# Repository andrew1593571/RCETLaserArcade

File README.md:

# Laser-Arcade-Project
All documentation of the Laser Arcade Project

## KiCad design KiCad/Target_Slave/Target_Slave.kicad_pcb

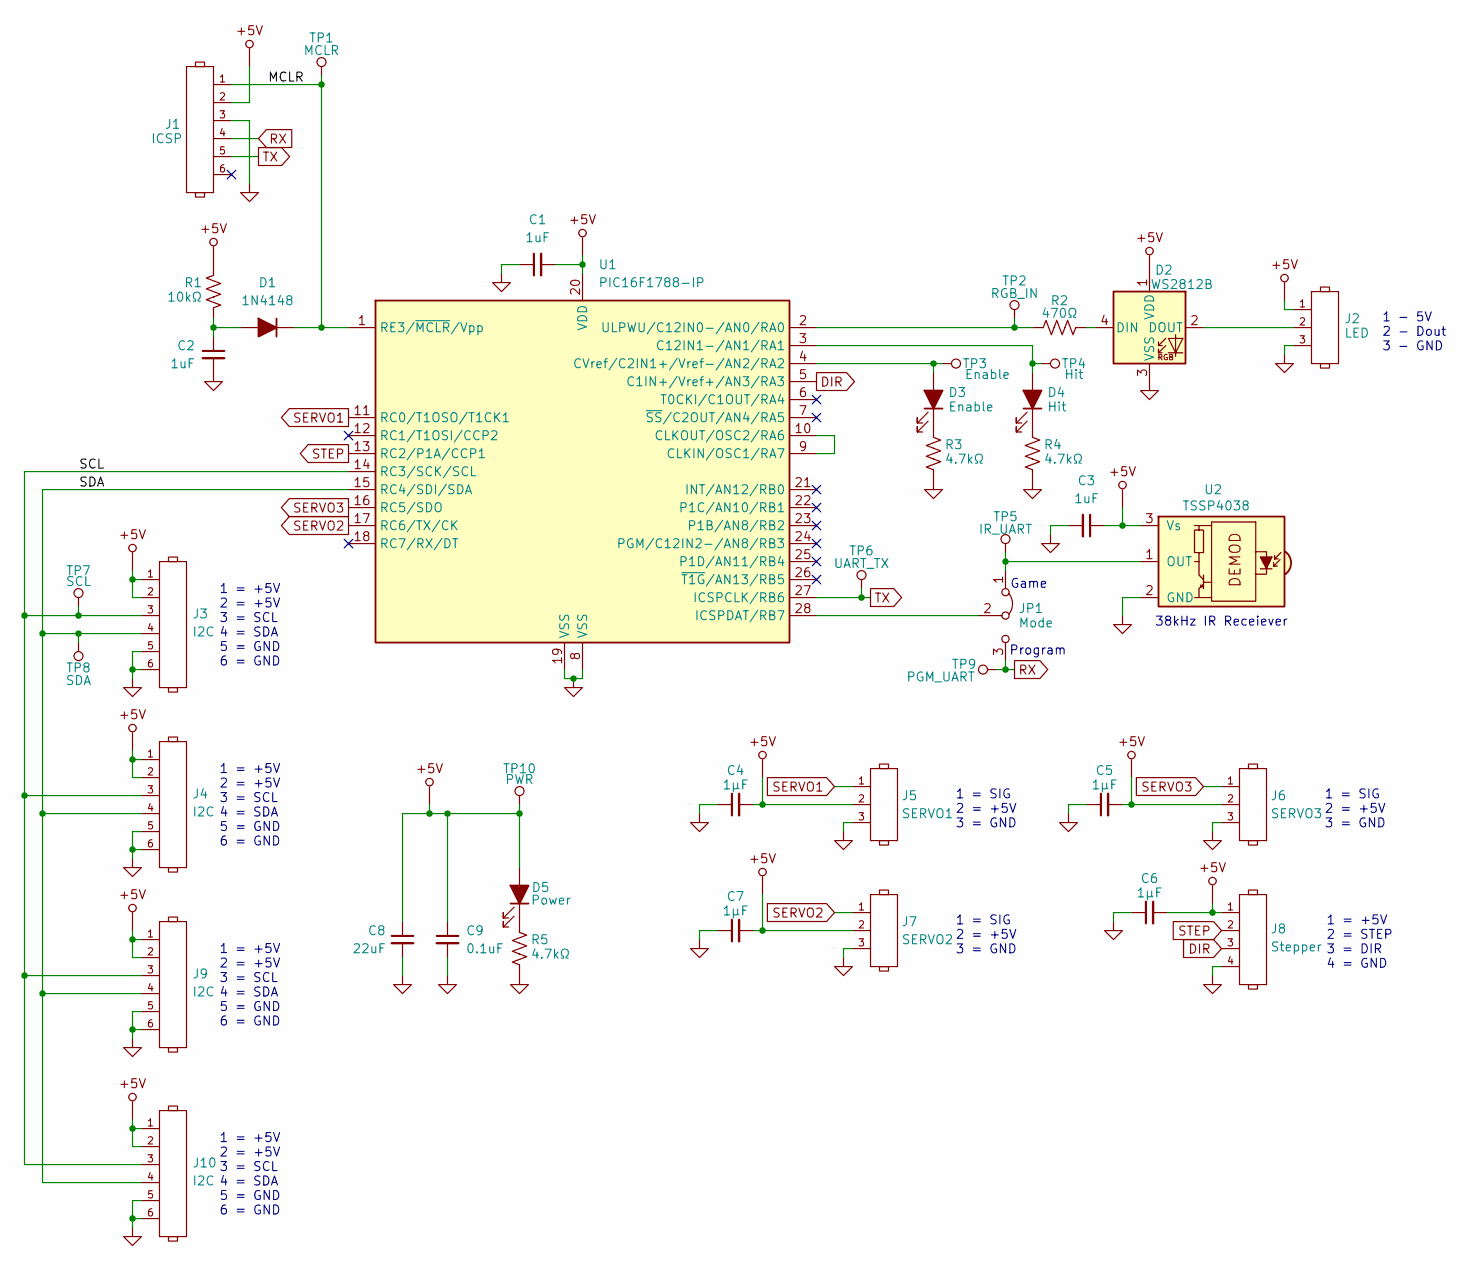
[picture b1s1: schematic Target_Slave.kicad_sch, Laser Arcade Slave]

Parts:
C1, C2, C3: 1uF; C_0805_2012Metric_Pad1.18x1.45mm_HandSolder
C4, C5, C6, C7: 1µF; C_0805_2012Metric_Pad1.18x1.45mm_HandSolder
C8: 22uF; C_0805_2012Metric_Pad1.18x1.45mm_HandSolder
C9: 0.1uF; C_0805_2012Metric_Pad1.18x1.45mm_HandSolder
D1: 1N4148; D_0805_2012Metric_Pad1.15x1.40mm_HandSolder
D2: WS2812B; LED_WS2812B_PLCC4_5.0x5.0mm_P3.2mm
D3: Enable; LED_0805_2012Metric_Pad1.15x1.40mm_HandSolder
D4: Hit; LED_0805_2012Metric_Pad1.15x1.40mm_HandSolder
D5: Power; LED_0805_2012Metric_Pad1.15x1.40mm_HandSolder
J1: ICSP; 1x6_100mil_Header
J2: LED; 1x3_100mil_Header_Locking
J3, J4, J9, J10: I2C; 1x6_100mil_Header
J5: SERVO1; 1x3_100mil_Header
J6: SERVO3; 1x3_100mil_Header
J7: SERVO2; 1x3_100mil_Header
J8: Stepper; 1x4_100mil_Header
JP1: Mode; 1x3_100mil_Header
R1: 10kΩ; R_0805_2012Metric_Pad1.20x1.40mm_HandSolder
R2: 470Ω; R_0805_2012Metric_Pad1.20x1.40mm_HandSolder
R3, R4, R5: 4.7kΩ; R_0805_2012Metric_Pad1.20x1.40mm_HandSolder
TP1: MCLR; 1x1_100mil_Header
TP2: RGB_IN; 1x1_100mil_Header
TP3: Enable; 1x1_100mil_Header
TP4: Hit; 1x1_100mil_Header
TP5: IR_UART; 1x1_100mil_Header
TP6: UART_TX; 1x1_100mil_Header
TP7: SCL; 1x1_100mil_Header
TP8: SDA; 1x1_100mil_Header
TP9: PGM_UART; 1x1_100mil_Header
TP10: PWR; 1x1_100mil_Header
U1: PIC16F1788-IP; SSOP-28
U2: TSSP4038; IR Receiver

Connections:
+5V: C1.2, C3.1, C4.2, C5.2, C6.2, C7.2, C8.1, C9.1, D2.1 (VDD), D5.2 (A), J1.2, J2.1, J3.1, J3.2, J4.1, J4.2, J5.2, J6.2, J7.2, J8.1, J9.1, J9.2, J10.1, J10.2, R1.1, TP10.1, U1.20 (VDD), U2.3 (Vs)
/MCLR: D1.1 (K), J1.1, TP1.1, U1.1 (RE3/~MCLR/Vpp)
/SCL: J3.3, J4.3, J9.3, J10.3, TP7.1, U1.14 (RC3/SCK/SCL)
/SDA: J3.4, J4.4, J9.4, J10.4, TP8.1, U1.15 (RC4/SDI/SDA)
DIR: J8.3, U1.5 (C1IN+/Vref+/AN3/RA3)
GND: C1.1, C2.2, C3.2, C4.1, C5.1, C6.1, C7.1, C8.2, C9.2, D2.3 (VSS), J1.3, J2.3, J3.5, J3.6, J4.5, J4.6, J5.3, J6.3, J7.3, J8.4, J9.5, J9.6, J10.5, J10.6, R3.2, R4.2, R5.2, U1.8 (VSS), U1.19 (VSS), U2.2 (GND)
unnamed: C2.1, D1.2 (A), R1.2
unnamed: D2.4 (DIN), R2.2
unnamed: D2.2 (DOUT), J2.2
unnamed: D3.2 (A), TP3.1, U1.4 (CVref/C2IN1+/Vref-/AN2/RA2)
unnamed: D3.1 (K), R3.1
unnamed: D4.2 (A), TP4.1, U1.3 (C12IN1-/AN1/RA1)
unnamed: D4.1 (K), R4.1
unnamed: D5.1 (K), R5.1
unnamed: JP1.1 (A), TP5.1, U2.1 (OUT)
unnamed: JP1.2 (C), U1.28 (ICSPDAT/RB7)
unnamed: U1.9 (CLKIN/OSC1/RA7), U1.10 (CLKOUT/OSC2/RA6)
unnamed: R2.1, TP2.1, U1.2 (ULPWU/C12IN0-/AN0/RA0)
RX: J1.4, JP1.3 (B), TP9.1
SERVO1: J5.1, U1.11 (RC0/T1OSO/T1CK1)
SERVO2: J7.1, U1.17 (RC6/TX/CK)
SERVO3: J6.1, U1.16 (RC5/SDO)
STEP: J8.2, U1.13 (RC2/P1A/CCP1)
TX: J1.5, TP6.1, U1.27 (ICSPCLK/RB6)

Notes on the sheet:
1 = +5V 2 = STEP 3 = DIR 4 = GND
1 = +5V 2 = +5V 3 = SCL 4 = SDA 5 = GND 6 = GND
Program
1 = SIG 2 = +5V 3 = GND
1 - 5V 2 - Dout 3 - GND
Game
38kHz IR Receiever

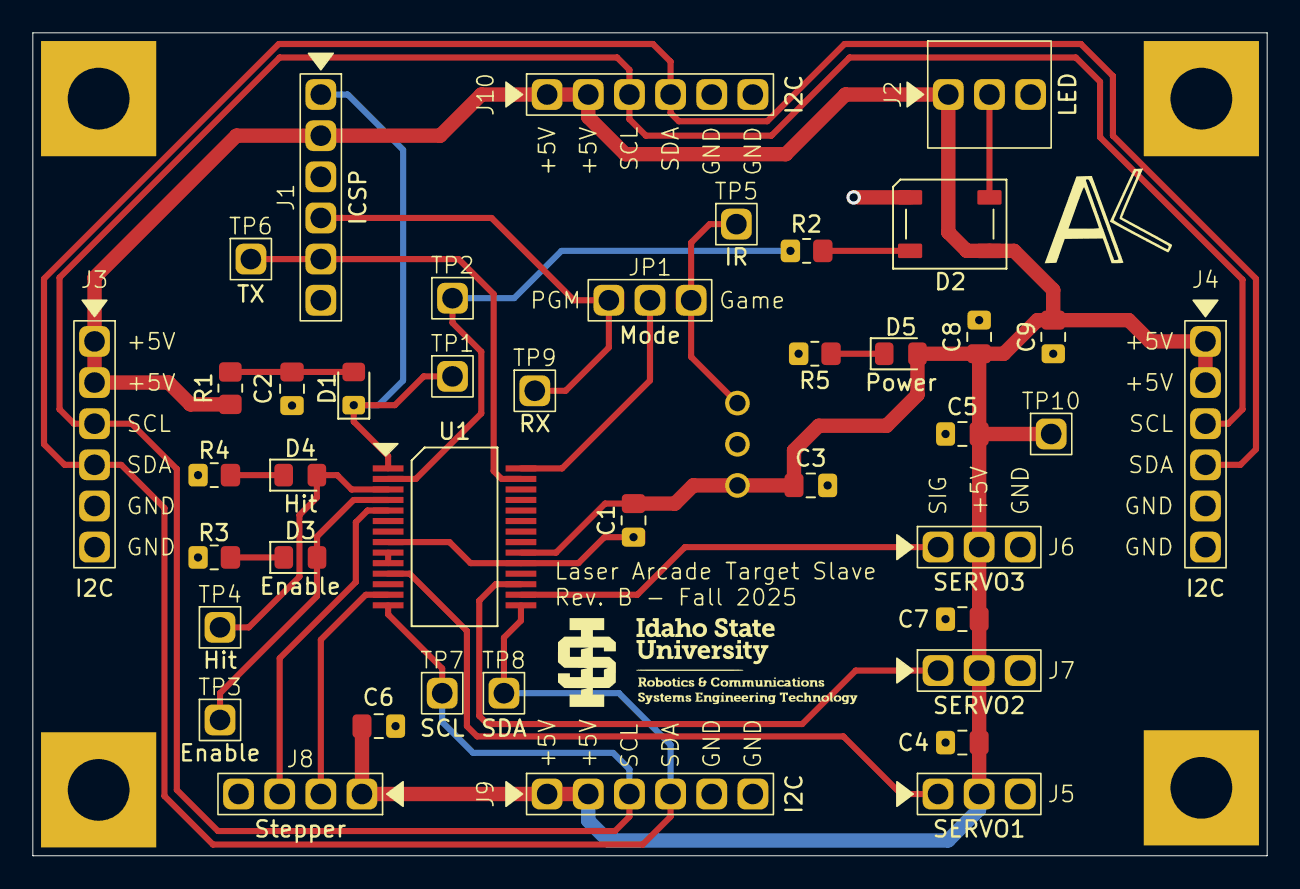
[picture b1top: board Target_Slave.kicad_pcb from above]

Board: 2 copper layers, 76.2 x 50.8 mm, 42 parts (1 on the bottom side), 24 nets.

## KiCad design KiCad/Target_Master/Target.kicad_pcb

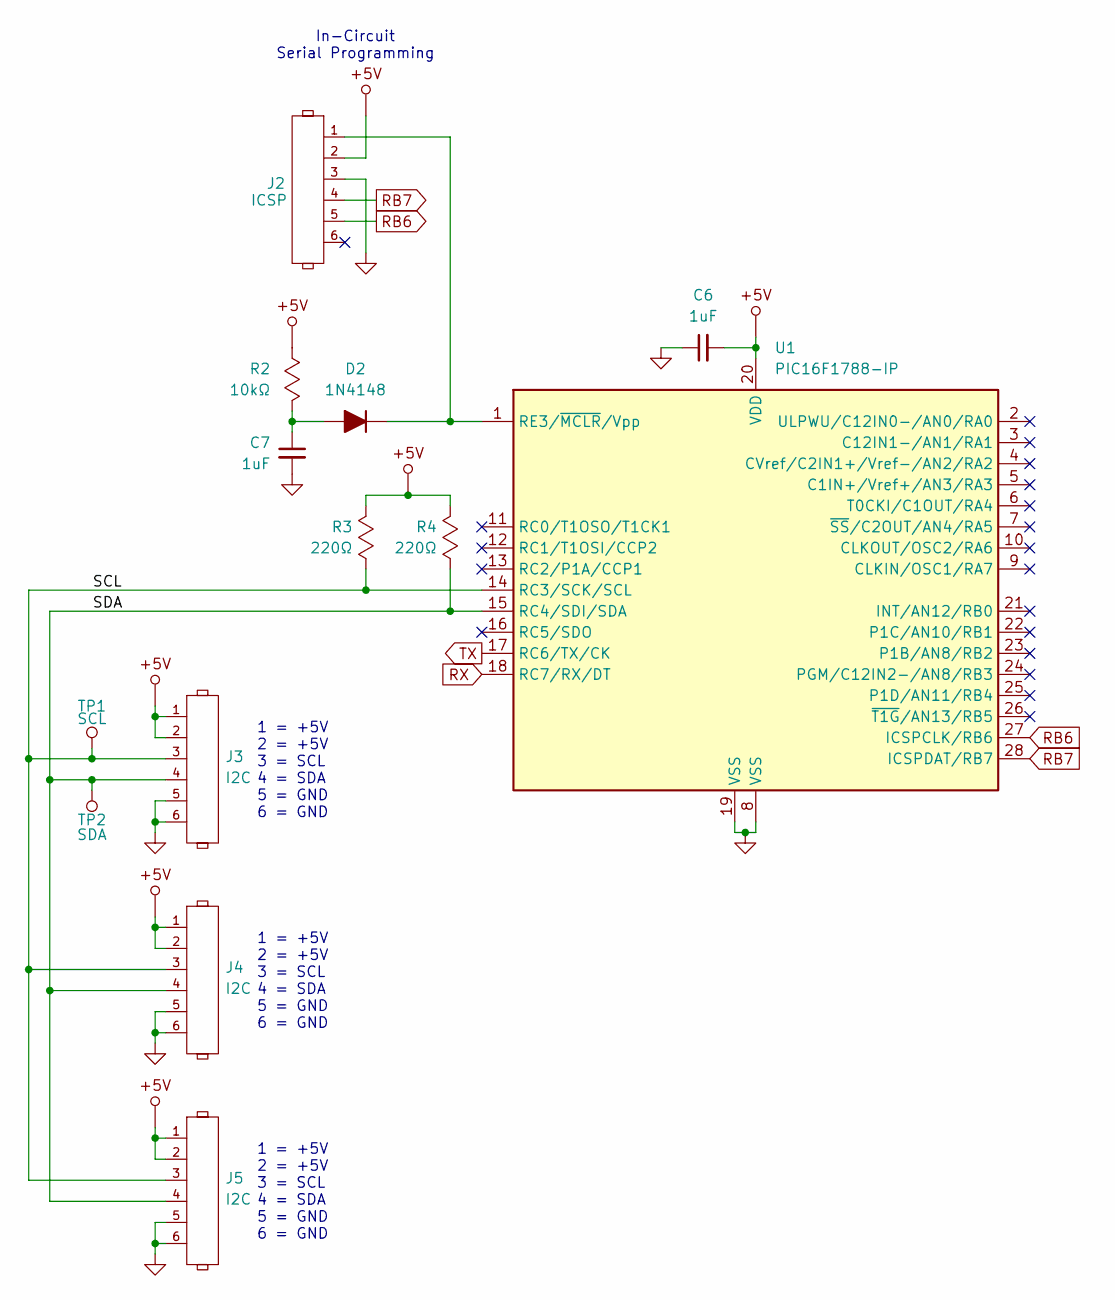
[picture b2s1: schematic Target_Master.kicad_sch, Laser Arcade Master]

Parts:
C6, C7: 1uF; C_0805_2012Metric_Pad1.18x1.45mm_HandSolder
D2: 1N4148; D_0805_2012Metric_Pad1.15x1.40mm_HandSolder
J2: ICSP; 1x6_100mil_Header
J3, J4, J5: I2C; 1x6_100mil_Header
R2: 10kΩ; R_0805_2012Metric_Pad1.20x1.40mm_HandSolder
R3, R4: 220Ω; R_0805_2012Metric_Pad1.20x1.40mm_HandSolder
TP1: SCL; 1x1_100mil_Header
TP2: SDA; 1x1_100mil_Header
U1: PIC16F1788-IP; SSOP-28

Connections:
+5V: C6.2, J2.2, J3.1, J3.2, J4.1, J4.2, J5.1, J5.2, R2.2, R3.1, R4.1, U1.20 (VDD); also elsewhere on the board
/Master/SCL: J3.3, J4.3, J5.3, R3.2, TP1.1, U1.14 (RC3/SCK/SCL)
/Master/SDA: J3.4, J4.4, J5.4, R4.2, TP2.1, U1.15 (RC4/SDI/SDA)
GND: C6.1, C7.2, J2.3, J3.5, J3.6, J4.5, J4.6, J5.5, J5.6, U1.8 (VSS), U1.19 (VSS); also elsewhere on the board
unnamed: C7.1, D2.2 (A), R2.1
unnamed: D2.1 (K), J2.1, U1.1 (RE3/~MCLR/Vpp)
RB6: J2.5, U1.27 (ICSPCLK/RB6)
RB7: J2.4, U1.28 (ICSPDAT/RB7)
RX: U1.18 (RC7/RX/DT); also elsewhere on the board
TX: U1.17 (RC6/TX/CK); also elsewhere on the board

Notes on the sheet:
In-Circuit Serial Programming
1 = +5V 2 = +5V 3 = SCL 4 = SDA 5 = GND 6 = GND

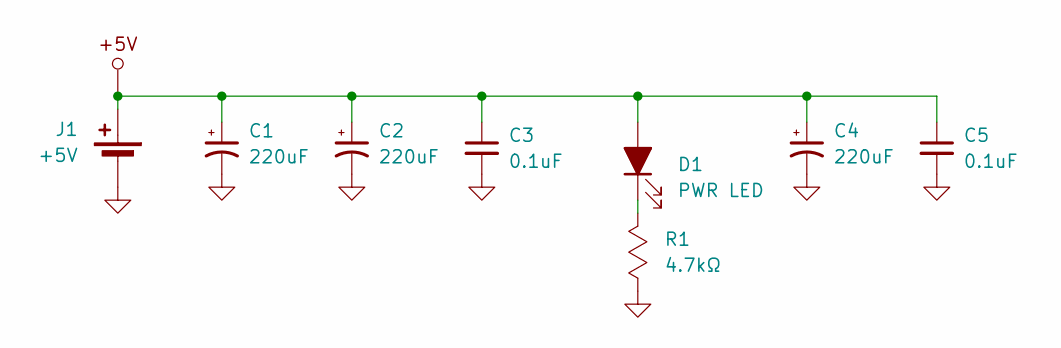
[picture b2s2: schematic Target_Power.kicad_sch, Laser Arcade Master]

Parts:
C1, C2, C4: 220uF; CP_Radial_D6.3mm_P2.50mm
C3, C5: 0.1uF; C_0805_2012Metric_Pad1.18x1.45mm_HandSolder
D1: PWR LED; LED_0805_2012Metric_Pad1.15x1.40mm_HandSolder
J1: +5V; AMASS_XT30PW-M_1x02_P2.50mm_Horizontal
R1: 4.7kΩ; R_0805_2012Metric_Pad1.20x1.40mm_HandSolder

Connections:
+5V: C1.1, C2.1, C3.1, C4.1, C5.1, D1.2 (A), J1.1 (+); also elsewhere on the board
GND: C1.2, C2.2, C3.2, C4.2, C5.2, J1.2 (-), R1.1; also elsewhere on the board
unnamed: D1.1 (K), R1.2

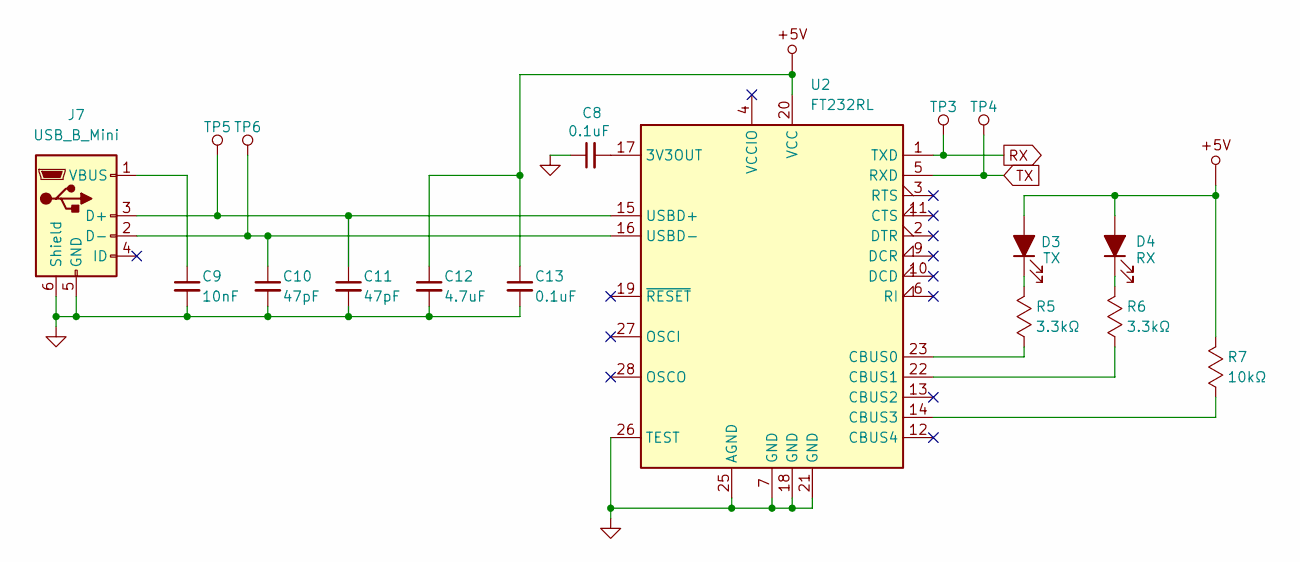
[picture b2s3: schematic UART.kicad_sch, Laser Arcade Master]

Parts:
C8, C13: 0.1uF; C_0805_2012Metric_Pad1.18x1.45mm_HandSolder
C9: 10nF; C_0805_2012Metric_Pad1.18x1.45mm_HandSolder
C10, C11: 47pF; C_0805_2012Metric_Pad1.18x1.45mm_HandSolder
C12: 4.7uF; C_0805_2012Metric_Pad1.18x1.45mm_HandSolder
D3: TX; LED_0805_2012Metric_Pad1.15x1.40mm_HandSolder
D4: RX; LED_0805_2012Metric_Pad1.15x1.40mm_HandSolder
J7: USB_B_Mini; USB_Micro-B_Amphenol
R5, R6: 3.3kΩ; R_0805_2012Metric_Pad1.20x1.40mm_HandSolder
R7: 10kΩ; R_0805_2012Metric_Pad1.20x1.40mm_HandSolder
TP3, TP4, TP5, TP6: 1x1_100mil_Header
U2: FT232RL; SSOP-28

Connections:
+5V: C12.1, C13.1, D3.2 (A), D4.2 (A), R7.2, U2.20 (VCC); also elsewhere on the board
GND: C8.1, C9.2, C10.2, C11.2, C12.2, C13.2, J7.5 (GND), J7.6 (Shield), U2.7 (GND), U2.18 (GND), U2.21 (GND), U2.25 (AGND), U2.26 (TEST); also elsewhere on the board
unnamed: D3.1 (K), R5.2
unnamed: D4.1 (K), R6.2
unnamed: C11.1, J7.3 (D+), TP5.1, U2.15 (USBD+)
unnamed: C10.1, J7.2 (D-), TP6.1, U2.16 (USBD-)
unnamed: C9.1, J7.1 (VBUS)
unnamed: C8.2, U2.17 (3V3OUT)
unnamed: R5.1, U2.23 (CBUS0)
unnamed: R6.1, U2.22 (CBUS1)
unnamed: R7.1, U2.14 (CBUS3)
RX: TP3.1, U2.1 (TXD); also elsewhere on the board
TX: TP4.1, U2.5 (RXD); also elsewhere on the board

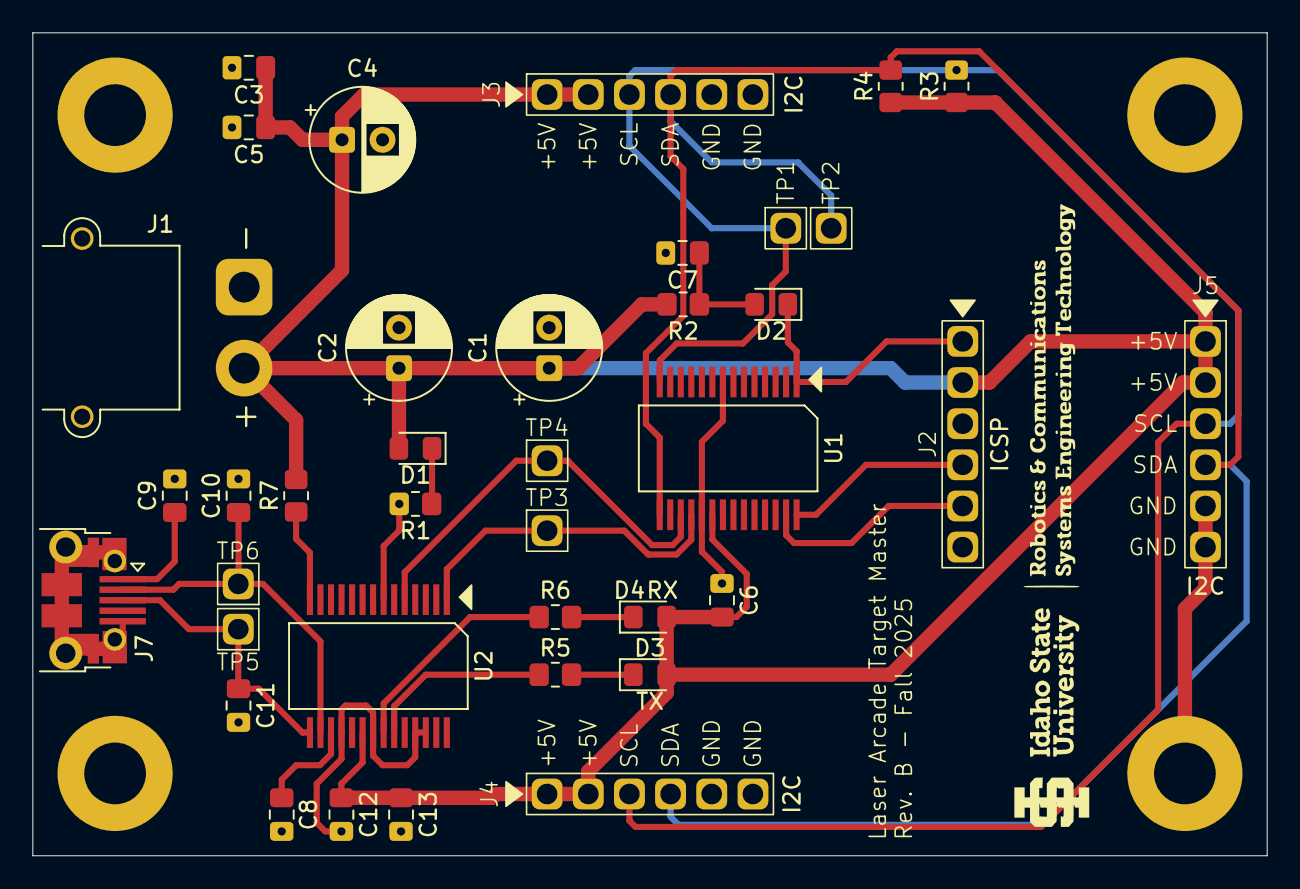
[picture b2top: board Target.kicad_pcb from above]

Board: 2 copper layers, 76.2 x 50.8 mm, 38 parts (0 on the bottom side), 20 nets.

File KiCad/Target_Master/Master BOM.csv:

"Id";"Designator";"Footprint";"Quantity";"Designation";"Supplier and ref";
1;"R7,R2";"R_0805_2012Metric_Pad1.20x1.40mm_HandSolder";2;"10kΩ";;;
2;"C2,C1,C6";"CP_Radial_D6.3mm_P2.50mm";3;"220uF";;;
3;"TP1,TP3,TP4,TP2";"1x1_100mil_Header";4;"~";;;
4;"U1";"SSOP-28";1;"PIC16F1788-IP";;;
5;"R5,R6";"R_0805_2012Metric_Pad1.20x1.40mm_HandSolder";2;"3.3kΩ";;;
6;"C7,C8,C13,C3";"C_0805_2012Metric_Pad1.18x1.45mm_HandSolder";4;"0.1uF";;;
7;"D3";"LED_0805_2012Metric_Pad1.15x1.40mm_HandSolder";1;"TX";;;
8;"J3,J5,J4";"1x4_100mil_Header";3;"I2C";;;
9;"D4";"LED_0805_2012Metric_Pad1.15x1.40mm_HandSolder";1;"RX";;;
10;"C9";"C_0805_2012Metric_Pad1.18x1.45mm_HandSolder";1;"10nF";;;
11;"D1";"LED_0805_2012Metric_Pad1.15x1.40mm_HandSolder";1;"PWR LED";;;
12;",";"";2;"";;;
13;"REF**,REF**";"M3 Mounting";2;"M3 Mounting";;;
14;"J1";"AMASS_XT30PW-M_1x02_P2.50mm_Horizontal";1;"+5V";;;
15;"L1";"L_0805_2012Metric_Pad1.15x1.40mm_HandSolder";1;"2uH";;;
16;"J6";"USB_Micro-B_Amphenol";1;"USB_B_Mini";;;
17;"U2";"SSOP-28";1;"FT232RL";;;
18;"J2";"1x6_100mil_Header";1;"ICSP";;;
19;"C4,C5";"C_0805_2012Metric_Pad1.18x1.45mm_HandSolder";2;"1uF";;;
20;"C12";"C_0805_2012Metric_Pad1.18x1.45mm_HandSolder";1;"4.7uF";;;
21;"C10,C11";"C_0805_2012Metric_Pad1.18x1.45mm_HandSolder";2;"47pF";;;
22;"R4,R3";"R_0805_2012Metric_Pad1.20x1.40mm_HandSolder";2;"220Ω";;;
23;"R1";"R_0805_2012Metric_Pad1.20x1.40mm_HandSolder";1;"4.7kΩ";;;
24;"D2";"Diode_0805";1;"1N4148";;;

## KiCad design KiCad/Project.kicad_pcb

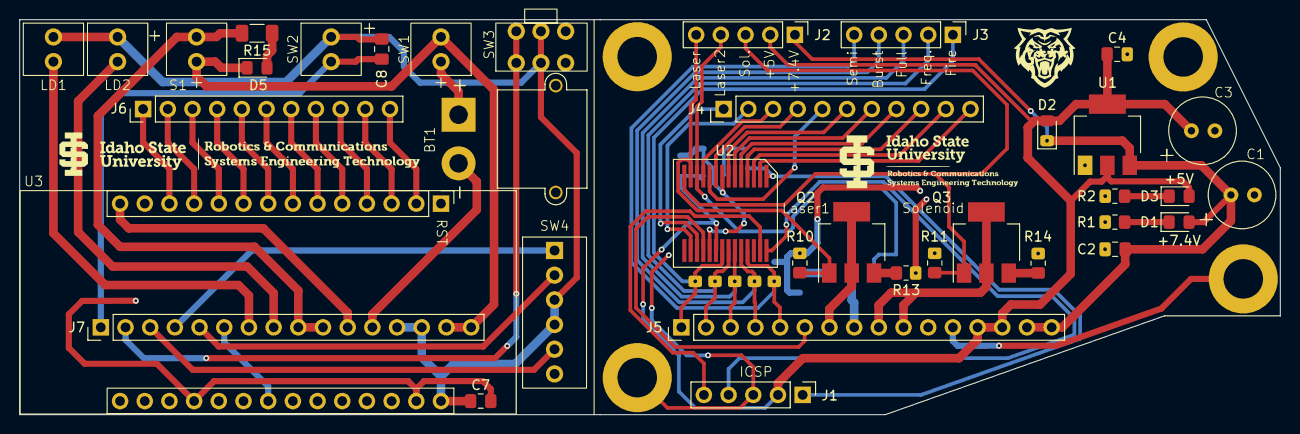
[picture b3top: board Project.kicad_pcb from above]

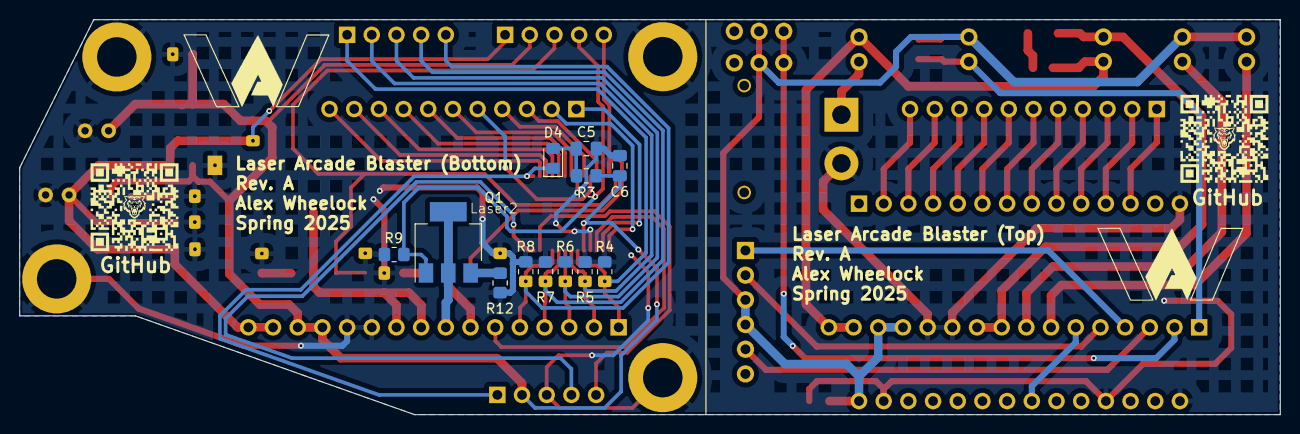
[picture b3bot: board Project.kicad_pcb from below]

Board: 2 copper layers, 129.7 x 40.6 mm, 49 parts (12 on the bottom side), 59 nets.

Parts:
BT1: 7.4V; Project_Battery_Connector
C1, C3: 220uF; Project_16V_220uF_Capacitor
C2, C4: 0.1uF; C_0805_2012Metric_Pad1.18x1.45mm_HandSolder
C5, C6, C7: 1uF; C_0805_2012Metric_Pad1.18x1.45mm_HandSolder
C8: 50pF; C_0805_2012Metric_Pad1.18x1.45mm_HandSolder
D1: +7.4V; LED_0805_2012Metric_Pad1.15x1.40mm_HandSolder
D2, D4, D5: 1N4148; D_0805_2012Metric_Pad1.15x1.40mm_HandSolder
D3: +5V; LED_0805_2012Metric_Pad1.15x1.40mm_HandSolder
J1: PinHeader_1x05_P2.54mm_Vertical
J2: Power & Output Test Points; PinHeader_1x05_P2.54mm_Vertical
J3: Inputs Test Points; PinHeader_1x05_P2.54mm_Vertical
J4, J6: PinHeader_1x11_P2.54mm_Vertical
J5, J7: PinHeader_1x16_P2.54mm_Vertical
LD1, LD2: Laser Diode; Project_Locking_Output_Header
Q1, Q2, Q3: BUK9832-55A; SOT-223-3_TabPin2
R1: 8.2kΩ; R_0805_2012Metric_Pad1.20x1.40mm_HandSolder
R2: 4.7kΩ; R_0805_2012Metric_Pad1.20x1.40mm_HandSolder
R3: 10kΩ; R_0805_2012Metric_Pad1.20x1.40mm_HandSolder
R4, R5, R6, R7, R8: 330Ω; R_0805_2012Metric_Pad1.20x1.40mm_HandSolder
R9, R10, R11: 100kΩ; R_0805_2012Metric_Pad1.20x1.40mm_HandSolder
R12, R13, R14: 0Ω; R_0805_2012Metric_Pad1.20x1.40mm_HandSolder
R15: 1kΩ; R_1206_3216Metric_Pad1.30x1.75mm_HandSolder
S1: Solenoid; Project_Locking_Output_Header
SW1: Power; Project_Locking_Output_Header
SW2: Fire; Project_Locking_Output_Header
SW3: Freq Select; Project_Blaster_Freq_Switch
SW4: Fire Select; Project_Locking_Header_1x06
U1: TLV1117-50; SOT-223-3_TabPin2
U2: PIC16F1788-IP; SSOP-28
U3: Audio Board; Project_Audio_Board

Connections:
+5V: C3.1, C4.1, C6.2, D2.2 (A), D3.2 (A), J1.2, J2.2, J5.13, J5.14, R3.2, U1.2 (VO), U2.20 (VDD)
+5V_Top: C7.2, C8.1, J7.13, J7.14, LD1.1 (A), LD2.1 (A), SW2.1, SW3.2 (B), SW4.3, SW4.4, U3.28 (VIN)
+7.4V: C1.1, C2.1, D1.2 (A), D2.1 (K), J2.1, J5.15, J5.16, U1.3 (VI)
+7.4V_Top: D5.1 (K), J7.15, J7.16, S1.1 (+), SW1.2 (B)
Burst: J3.4, J5.4, R7.1, U2.24 (PGM/C12IN2-/AN8/RB3)
Burst_Top: J7.4, SW4.1
Fire: J3.1, J5.1, R4.1, U2.21 (INT/AN12/RB0)
Fire_Top: C8.2, J7.1, SW2.2
Frequency Select: J3.2, J5.2, R5.1, U2.22 (P1C/AN10/RB1)
Frequency Select_Top: J7.2, SW3.1 (A)
Full-Auto: J3.3, J5.3, R6.1, U2.23 (P1B/AN8/RB2)
Full-Auto_Top: J7.3, SW4.5
GND: BT1.2 (-), C1.2, C2.2, C3.2, C4.2, C5.2, C6.1, C7.1, J1.3, J5.11, J5.12, J7.11, J7.12, R1.1, R2.1, R4.2, R5.2, R6.2, R7.2, R8.2, R9.2, R10.2, R11.2, R12.2, R13.2, R14.2, U1.1 (GND), U2.8 (VSS), U2.19 (VSS), U3.14 (GND), U3.15 (GND), U3.18 (GND), U3.27 (GND)
Laser/PWM: J5.7, Q2.2 (D)
Laser/PWM2: J5.8, Q1.2 (D)
Laser/PWM2_Top: J7.8, LD2.2 (K)
Laser/PWM_Top: J7.7, LD1.2 (K)
unnamed: BT1.1 (+), SW1.1 (A)
unnamed: D1.1 (K), R1.2
unnamed: D3.1 (K), R2.2
unnamed: C5.1, D4.2 (A), R3.1
unnamed: D4.1 (K), J1.1, U2.1 (RE3/~MCLR/Vpp)
unnamed: D5.2 (A), R15.2
unnamed: J2.4, Q1.1 (G), R9.1, U2.12 (RC1/T1OSI/CCP2)
unnamed: Q1.3 (S), R12.1
unnamed: J2.5, Q2.1 (G), R10.1, U2.13 (RC2/P1A/CCP1)
unnamed: Q2.3 (S), R13.1
unnamed: J2.3, Q3.1 (G), R11.1, U2.14 (RC3/SCK/SCL)
unnamed: Q3.3 (S), R14.1
RB6: J1.5, U2.27 (ICSPCLK/RB6)
RB7: J1.4, U2.28 (ICSPDAT/RB7)
Semi-Auto: J3.5, J5.5, R8.1, U2.25 (P1D/AN11/RB4)
Semi-Auto_Top: J7.5, SW4.2
Solenoid: J5.9, J5.10, Q3.2 (D)
Solenoid_Top: J7.9, J7.10, R15.1, S1.2 (-)
TRIG0: J4.11, U2.2 (ULPWU/C12IN0-/AN0/RA0)
TRIG0_Top: J6.11, U3.2 (TRIG0)
TRIG1: J4.10, U2.3 (C12IN1-/AN1/RA1)
TRIG1_Top: J6.10, U3.3 (TRIG1)
TRIG2: J4.9, U2.4 (CVref/C2IN1+/Vref-/AN2/RA2)
TRIG2_Top: J6.9, U3.4 (TRIG2)
TRIG3: J4.8, U2.5 (C1IN+/Vref+/AN3/RA3)
TRIG3_Top: J6.8, U3.5 (TRIG3)
TRIG4: J4.7, U2.6 (T0CKI/C1OUT/RA4)
TRIG4_Top: J6.7, U3.6 (TRIG4)
TRIG5: J4.6, U2.7 (~SS/C2OUT/AN4/RA5)
TRIG5_Top: J6.6, U3.7 (TRIG5)
TRIG6: J4.5, U2.10 (CLKOUT/OSC2/RA6)
TRIG6_Top: J6.5, U3.8 (TRIG6)
TRIG7: J4.4, U2.9 (CLKIN/OSC1/RA7)
TRIG7_Top: J6.4, U3.9 (TRIG7)
TRIG8: J4.3, U2.11 (RC0/T1OSO/T1CK1)
TRIG8_Top: J6.3, U3.10 (TRIG8)
TRIG9: J4.2, U2.16 (RC5/SDO)
TRIG9_Top: J6.2, U3.11 (TRIG9)
TRIG10: J4.1, U2.17 (RC6/TX/CK)
TRIG10_Top: J6.1, U3.12 (TRIG10)
VOL+: J5.6, U2.18 (RC7/RX/DT)
VOL+_Top: J7.6, U3.21 (VOL+)

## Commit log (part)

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2025-04-04 Initialize repo with current project materials
2025-04-04 adding/fixing UART in master schematic.
2025-04-10 Add gitignore and gitattributes
2025-04-10 Remove .X Folders
2025-04-10 Init Visual Basic Arcade Control Program
2025-04-10 Add serial port icon as resource
2025-04-10 Add Serial Port, Connect and Disconnect from Serial, send device verification command
2025-04-10 Change Include file names to the MASTER include files
2025-04-11 Add UART setup for 9600 baud, enable UART receive interrupt
2025-04-11 UART RX/TX setup, Device verification command response
2025-04-11 Updated blaster schematic
2025-04-11 Interpret UART commands to set flags for I2C to handle, Add UARTSENDSCORE subroutine
2025-04-11 receive device verification command
2025-04-14 Finalized schematics
2025-04-14 Init LaserArcade and ArcadeTarget classes, Move serial communications into LaserArcade class, enable specific targets, enable random targets
2025-04-14 Disable targets, timed disable of targets
2025-04-14 Test gameplay
2025-04-15 started working on blaster PCB
2025-04-15 Init ArcadeConfigurationForm
2025-04-15 Default Configuration, modify configuration
2025-04-15 Save and Open configurations
2025-04-15 working on the PCB for the blaster
2025-04-15 Control form GUI, track player scores
2025-04-16 got a lot done on the blaster PCB
2025-04-16 blaster PCB is nearly finished
2025-04-16 Target Slave PCB
2025-04-17 Add Silkscreen text, Add logos
2025-04-17 added title block and logo
2025-04-17 Master PCB design, Slave board logos
2025-04-17 Master board silkscreen and gerber files
2025-04-17 kiCad backup files
2025-04-17 recovered some lost parts of the schematic, still needs a bit of work to get back
2025-04-18 fixed the schematics, and got the new components added into the PCB, need to rerun a lot of traces.
2025-04-18 Target Master Gerbers
2025-04-18 Slave Gerbers
2025-04-18 PCB nearly done for the blaster
2025-04-21 finished blaster PCB
2025-04-22 Slave I2C protocol, enabling and disabling target, i2c read response, interrupt on change ISR
2025-04-22 Single Target I2C, interpret scores, send scores back via UART
2025-04-22 Change Slave I2C address using dipswitches
2025-04-22 Add Two I2C targets communications protocol
2025-04-22 Update file headers, add comments, remove defined general registers not being used
2025-04-22 Add target slots three through eight to master
2025-04-22 Fix crash when score received through UART
2025-04-23 Clear unused general registers
2025-04-23 Update comments and file headers
2025-04-23 Renamed slave setup include file to remove _001
2025-04-23 Update which LEDs are on and when
2025-04-23 Add ability to stop game, Disable all targets if closed while game in progress
2025-04-23 Move updating player scores on GUI from GameTimer tick to separate timer
2025-04-23 File Headers, code comments, 127 max targets, init about form
2025-04-23 Add information to about form, add clickable link to github
2025-04-23 Prevent changes in connection during a game, require device verification again after disconnect
2025-04-24 blaster solenoid mount, speaker box, and barrel designed
2025-04-29 Got all of the 3D modeling for the blaster completed
2025-04-29 Updated blaster code comments, tables, and headings.
2025-05-04 updated the blaster code to work with the PCB correctly
2025-05-05 fixed the blaster code in GitHub
2025-05-07 put serial reads and writes into Try-catch
2025-05-07 comments, add LaserArcade event for unexpected COM disconnects, start COM port refresh timer at load
2025-05-07 making sure everything is up to date
2025-05-07 Correct schematic graphic issues on Slave
2025-05-07 Add titleblock to target PCBs
2025-05-07 pushing final changes to the project
2025-05-08 Add Master Report Images
2025-05-08 Add Slave report images
2025-05-08 Add target 3D Models
2025-05-08 Add bengal icon to all forms
2025-05-08 Publish VB and create software install files
2025-05-08 Add Spring 2025 Project Report and Presentation
2025-05-08 Random KiCad files
2025-10-21 Add Kicad backup and lock files to gitignore
2025-10-21 Apply new gitignore to remove KiCad backup and lock files
2025-10-22 Move I2C notes to References
2025-10-22 Move Datasheets into References
2025-10-22 Move Audio Files to References
2025-10-22 Moved Blaster KiCad files into separate folder
2025-10-22 Moved Logos and Titleblocks to Libraries folder
2025-10-22 Split Target and Blaster 3D files into folders
2025-10-22 Move Fall 2024 and Spring 2025 into Documentation
2025-10-22 Archive Target Slave as Revision A
2025-10-22 Archive Blaster KiCad files as Revision A
2025-10-22 Update KiCad Titleblock
2025-10-22 Target Slave Revision B schematic update
2025-10-22 Add Target Slave Revision B Schematic PDF
2025-10-22 Add WS2812B Datasheet for reference
2025-11-24 adding updated setup subroutines for where I am in the coding phase. This includes initial setup as well as I2C initialized values within EEPROM
2025-12-02 Adding I2C code for the change LED command, also adding the setup code for EUSART
2025-12-03 added EUSART commands control for RX'
2025-12-08 adding most of the EUSART code as well as some of the setup for the PSMC module for the servos
2025-12-08 adding PSMC module code, changed some of the I2C code for trouble shooting purposes still need to have working and tested code for I2C
2025-12-16 Started adding the I2C Read Method: -In Events/Fields added result events such as success or failed -Started updating the the command method so that it parses the I2C Read
2025-12-16 -Added small function to remember the last event that was received in order to parse later -Added a call to parse I2C Read Response -Added header to the Data Parsing, explaining expected response & w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
2025-12-16 -Raise event if the SerialPort is not open
2025-12-17 -Data parsing section
2025-12-18 Adding any updated master code that I changed '
2026-03-10 CODE!
2026-05-07 end of the semester changes
2026-05-07 end of the semester backup
